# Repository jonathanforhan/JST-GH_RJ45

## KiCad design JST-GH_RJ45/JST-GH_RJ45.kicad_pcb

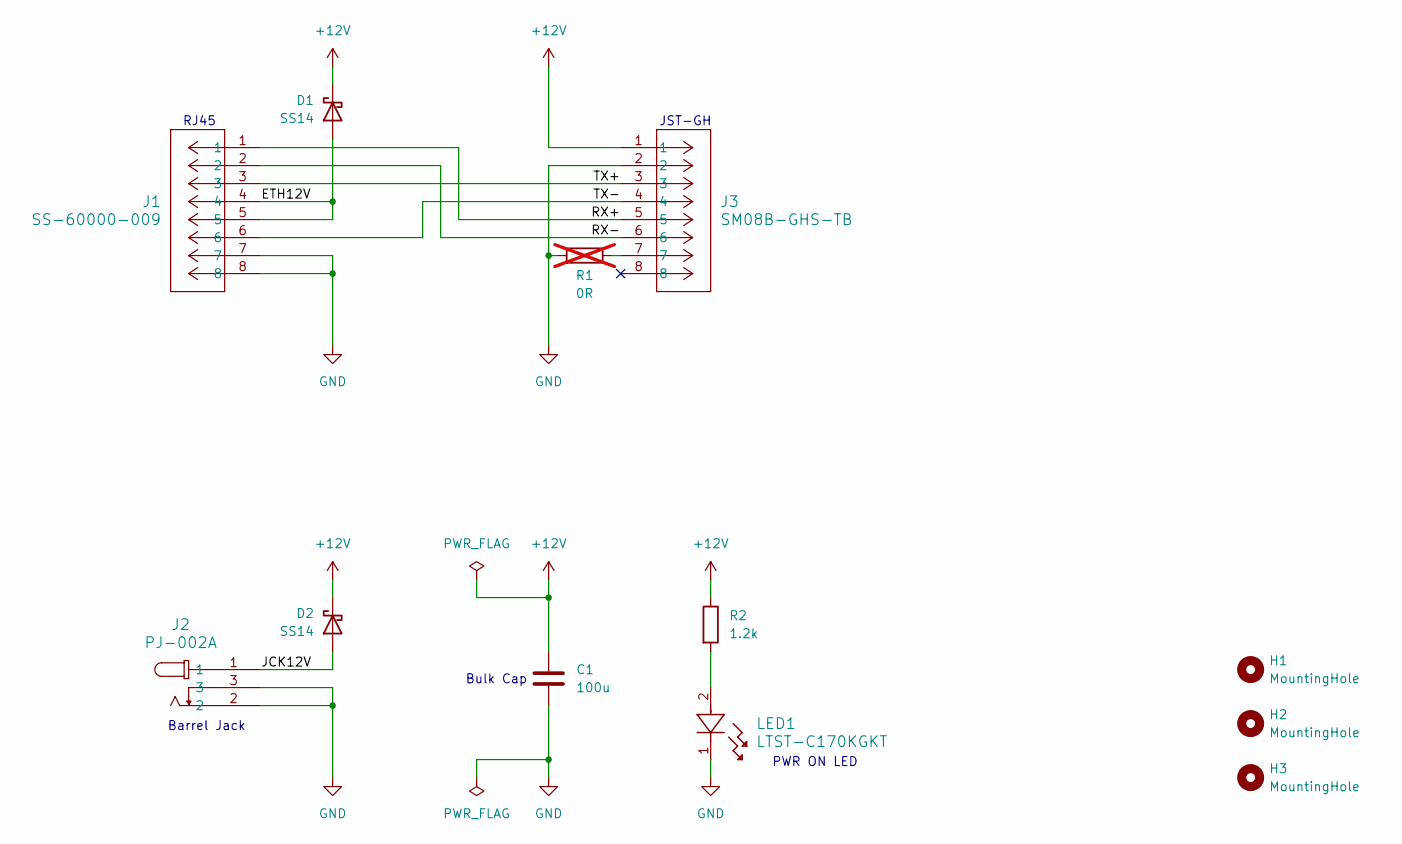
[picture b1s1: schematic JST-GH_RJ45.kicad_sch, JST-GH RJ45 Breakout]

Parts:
C1: 100u; C_1210_3225Metric_Pad1.33x2.70mm_HandSolder
D1, D2: SS14; D_SMA_Handsoldering
H1, H2, H3: MountingHole; MountingHole_2.7mm_M2.5
J1: SS-60000-009; CONN8_SS-60000_STW
J2: PJ-002A; CUI_PJ-002A
J3: SM08B-GHS-TB; CONN_SM08B-GHS-TB_JST
LED1: LTST-C170KGKT; LED_LTST-C170KGKT_LTO
R1: 0R; R_0805_2012Metric_Pad1.20x1.40mm_HandSolder; not fitted
R2: 1.2k; R_0805_2012Metric_Pad1.20x1.40mm_HandSolder

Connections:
+12V: C1.1, D1.1 (K), D2.1 (K), J3.1, R2.1
/ETH12V: D1.2 (A), J1.4, J1.5
/JCK12V: D2.2 (A), J2.1
/RX+: J1.1, J3.5
/RX-: J1.2, J3.6
/TX+: J1.3, J3.3
/TX-: J1.6, J3.4
GND: C1.2, J1.7, J1.8, J2.2, J2.3, J3.2, LED1.1, R1.2
unnamed: J3.7, R1.1
unnamed: LED1.2, R2.2

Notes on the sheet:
Bulk Cap
Barrel Jack
RJ45
JST-GH
PWR ON LED

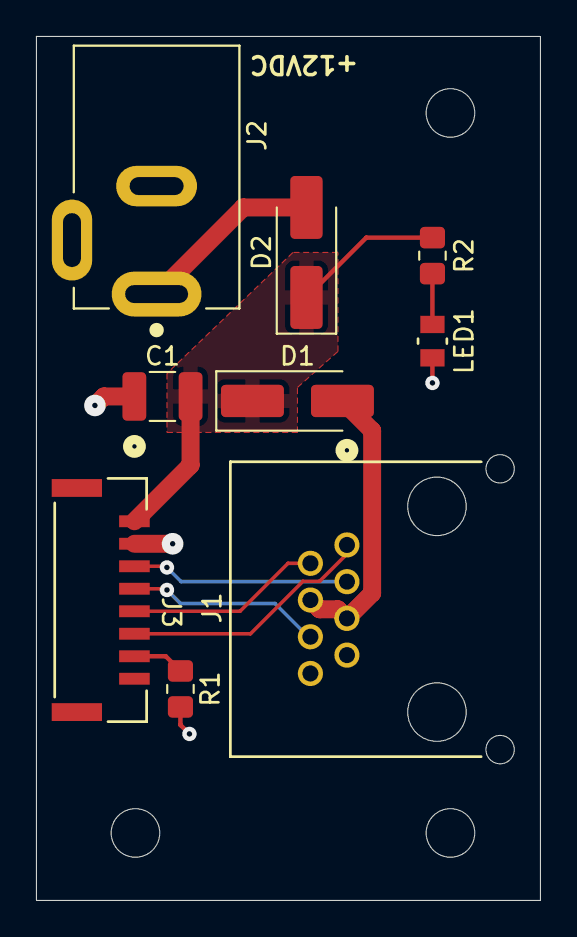
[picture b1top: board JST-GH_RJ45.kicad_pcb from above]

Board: 2 copper layers, 28.0 x 48.0 mm, 12 parts (0 on the bottom side), 10 nets.

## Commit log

2026-02-10 add 3D models to project
2026-02-18 fix silkscreen for JLCPCB
